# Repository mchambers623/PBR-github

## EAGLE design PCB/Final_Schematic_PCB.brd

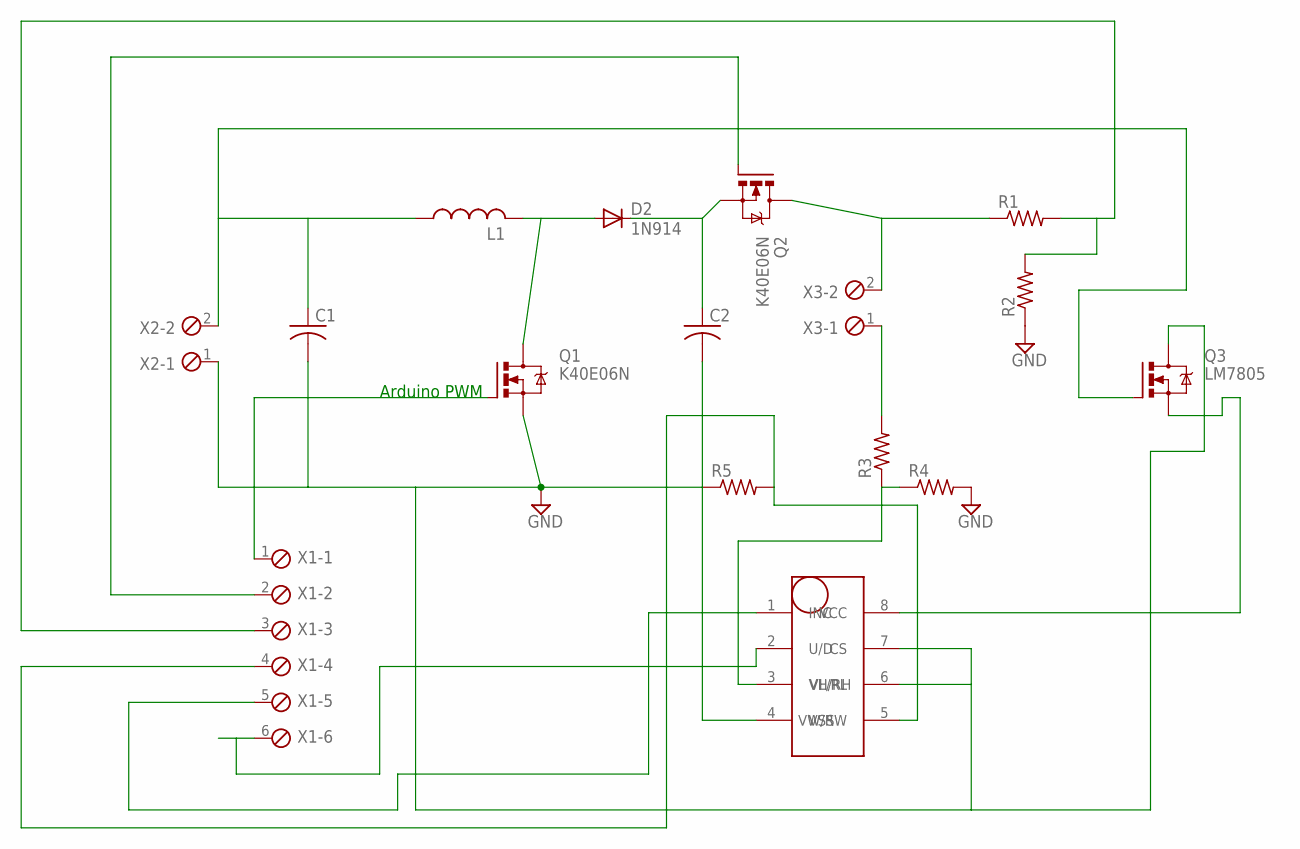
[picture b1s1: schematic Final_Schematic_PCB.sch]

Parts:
C1, C2: C-US050-045X075; C050-045X075
D2: 1N914; DO41-10
L1: L-US0207/5V; 0207/5V
Q1, Q2: K40E06N; TO220BV
Q3: LM7805; TO220BV
R1, R2, R3, R4, R5: R-US_0204/5; 0204/5
U$1: 1KDP
X1: MPT6; 6POL254
X2, X3: MPT2; 2POL254

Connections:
GND: C1.2, C2.2, Q1.S, Q3.D, R2.1, R4.2, R5.1, U$1.4 (VSS), U$1.6 (VL/RL), U$1.7 (CS), X2.1
unnamed: C1.1, L1.1, Q3.G, X2.2
unnamed: D2.A, L1.2, Q1.D
unnamed: C2.1, D2.C, Q2.S
unnamed: R1.2, R2.2, X1.3
unnamed: Q3.S, U$1.8 (VCC)
unnamed: Q2.D, R1.1, X3.2
unnamed: R3.2, X3.1
unnamed: R3.1, R4.1, U$1.3 (VH/RH)
unnamed: R5.2, U$1.5 (VW/RW), X1.4
unnamed: Q1.G, X1.1
unnamed: Q2.G, X1.2
unnamed: U$1.1 (INC), X1.5
unnamed: U$1.2 (U/D), X1.6

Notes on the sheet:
Arduino PWM

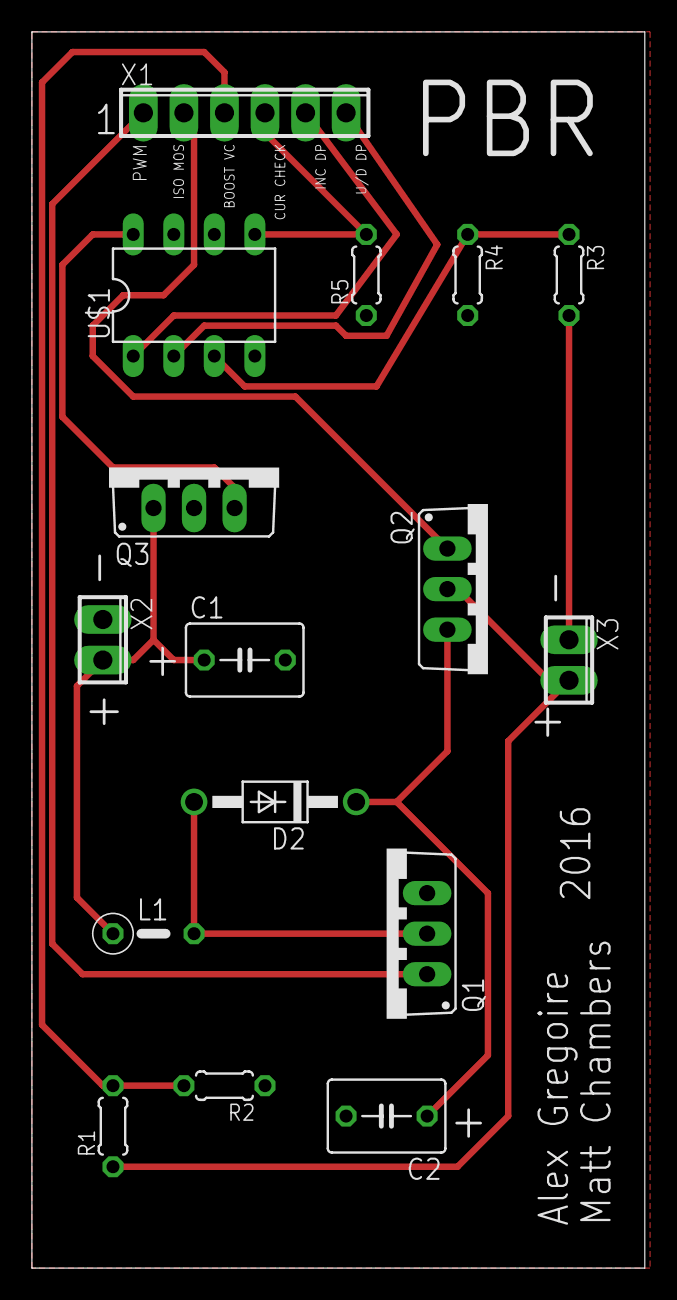
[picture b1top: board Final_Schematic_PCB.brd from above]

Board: 2 copper layers, 38.4 x 77.5 mm, 16 parts (0 on the bottom side), 14 nets.

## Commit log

2015-11-06 :boom::camel: Added .gitattributes & .gitignore files
2015-11-06 Figured it out finally......
2015-11-06 Cleaning up...
2015-11-10 got stuff working together
2015-11-11 Added some features
    Lost digital pot. Added LED's to show stage.
2015-11-11 Added initial voltage recognition
    Decides state based on initial battery voltage reading
2015-11-11 Scaled Timed Charging Cycle
    Switches between stages with a 10s interval
2015-11-14 optimized with solder board
2015-11-16 optimized more things
2015-12-08 Added some comments
2015-12-14 AA Charging Added
2015-12-16 Merged Codes
    Also added commenting and defines
2015-12-16 Tried to get some structs working
2015-12-16 Final Touches
2015-12-16 Final
